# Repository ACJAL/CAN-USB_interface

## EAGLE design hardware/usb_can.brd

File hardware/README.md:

# Hardware
---

Fichiers de conception de la carte éléctronique. Le PCB a été réalisé avec le logiciel *eagle* de *CADsoft*.

+ [Schéma *fichier eagle SCH*](usb_can.sch)
+ [Schéma *fichier PDF*](usb_can_sch.pdf)
+ [Routage *fichier eagle BRD*](usb_can.brd)
+ [DOC](usb_can_doc_hard.pdf) (La documention de la carte a été réalisée avec *LaTeX*)

## Synoptique de la carte

Le coeur de l'interface est un PIC18F2580. Microcontroleur 8 bits, possédant un module bus CAN intégré.

La partie communication USB est réalisé par un MCP2210. Ce composant est une interface USB vers SPI qui nécessite très peu de composants pour être mis en oeuvre.

L'interface bus CAN (liaison matérielle) est réalisée par un MCP2561.

Enfin, un interrupteur sur la carte éléctronique permet de *terminer* ou non le bus avec une résistance de 120 Ohms.

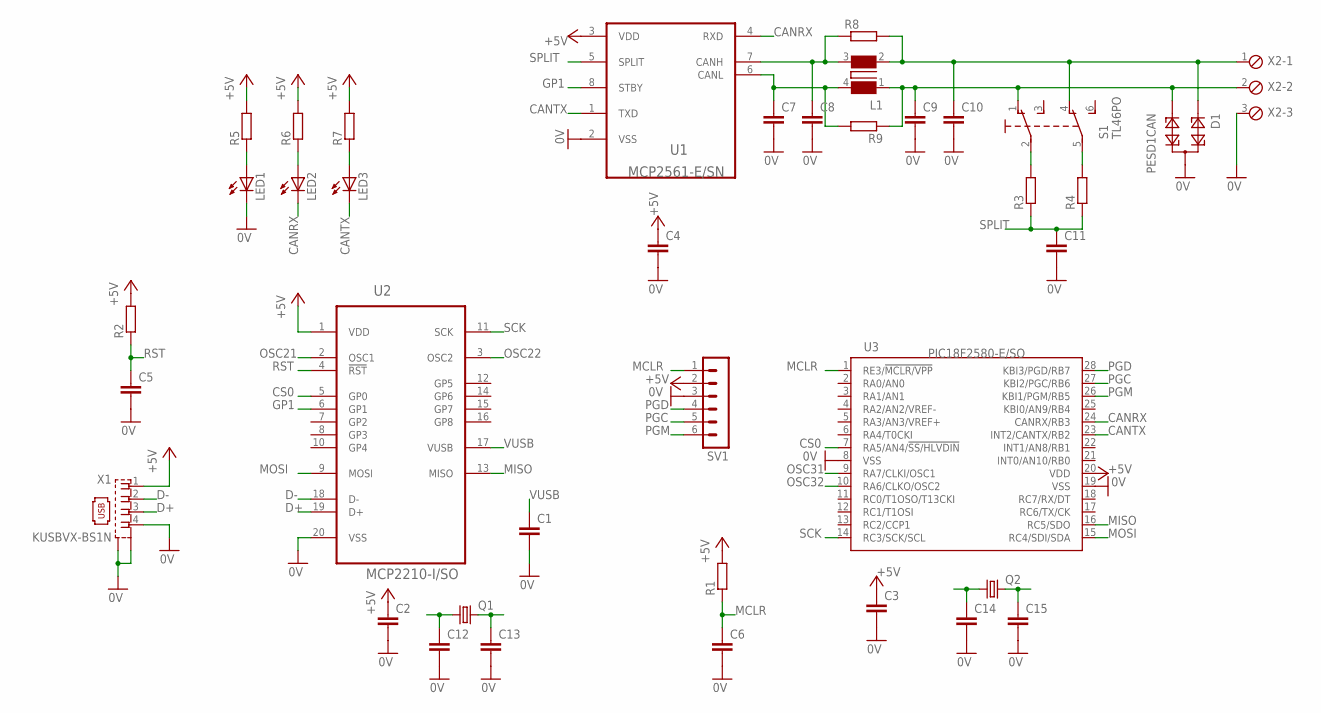
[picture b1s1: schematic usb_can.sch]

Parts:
C1: C-EUC1210; C1210
C2, C3, C4, C5, C6, C7, C8, C9, C10, C11, C12, C13, C14, C15: C-EUC0805; C0805
D1: PESD1CAN; SOT23
L1: WE-SLM-744242510; WE-SLM
LED1, LED2, LED3: LED3MM
Q1, Q2: CRYSTALHC49UP; HC49UP
R1, R2, R5, R6, R7: R-EU_R0805; R0805
R3, R4, R8, R9: R-EU_MELF0204W; MINI_MELF-0204W
S1: TL46PO; TL4XPO
SV1: MA06-1
U1: MCP2561-E/SN; SOIC127P600X175-8N
U2: MCP2210-I/SO; SOIC127P1030X265-20N
U3: PIC18F2580-E/SO; SO28W
X1: KUSBVX-BS1N
X2: MPT3; 3POL254

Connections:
0V: C1.2, C2.2, C3.2, C4.2, C5.2, C6.2, C7.2, C8.2, C9.2, C10.2, C11.2, C12.2, C13.2, C14.2, C15.2, D1.3, LED1.K (C), SV1.3, U1.2 (VSS), U2.20 (VSS), U3.8 (VSS), U3.19 (VSS), X1.4, X1.M1 (S1), X1.M2 (S2), X2.3
+5V: C2.1, C3.1, C4.1, R1.2, R2.2, R5.2, R6.2, R7.2, SV1.2, U1.3 (VDD), U2.1 (VDD), U3.20 (VDD), X1.1
CANRX: LED2.K (C), U1.4 (RXD), U3.24 (CANRX/RB3)
CANTX: LED3.K (C), U1.1 (TXD), U3.23 (INT2/CANTX/RB2)
CS0: U2.5 (GP0), U3.7 (RA5/AN4/!SS/HLVDIN)
D+: U2.19 (D+), X1.3
D-: U2.18 (D-), X1.2
GP1: U1.8 (STBY), U2.6 (GP1)
MCLR: C6.1, R1.1, SV1.1, U3.1 (RE3/!MCLR/VPP)
MISO: U2.13 (MISO), U3.16 (RC5/SDO)
MOSI: U2.9 (MOSI), U3.15 (RC4/SDI/SDA)
unnamed: R3.2, S1.2
unnamed: LED3.A, R7.1
unnamed: R4.2, S1.5 (P1)
unnamed: C8.1, L1.3 (2), R8.1, U1.7 (CANH)
unnamed: C7.1, L1.4, R9.2, U1.6 (CANL)
unnamed: C9.1, D1.2, L1.1 (3), R9.1, S1.1 (O), X2.2
unnamed: C10.1, D1.1, L1.2 (1), R8.2, S1.4 (O1), X2.1
unnamed: LED2.A, R6.1
unnamed: LED1.A, R5.1
OSC21: C12.1, Q1.1, U2.2 (OSC1)
OSC22: C13.1, Q1.2, U2.3 (OSC2)
OSC31: C14.1, Q2.1, U3.9 (RA7/CLKI/OSC1)
OSC32: C15.1, Q2.2, U3.10 (RA6/CLKO/OSC2)
PGC: SV1.5, U3.27 (KBI2/PGC/RB6)
PGD: SV1.4, U3.28 (KBI3/PGD/RB7)
PGM: SV1.6, U3.26 (KBI1/PGM/RB5)
RST: C5.1, R2.1, U2.4 (!RST)
SCK: U2.11 (SCK), U3.14 (RC3/SCK/SCL)
SPLIT: C11.1, R3.1, R4.1, U1.5 (SPLIT)
VUSB: C1.1, U2.17 (VUSB)

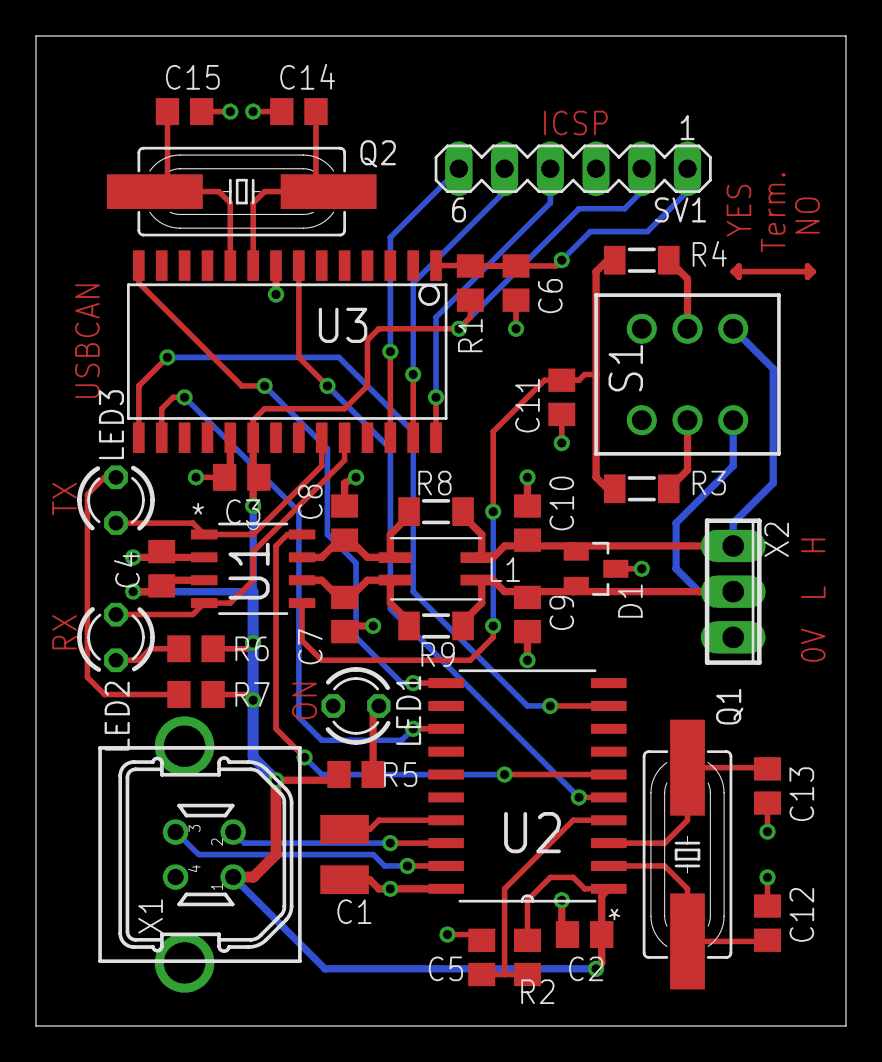
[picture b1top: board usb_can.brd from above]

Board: 2 copper layers, 45.0 x 55.0 mm, 38 parts (0 on the bottom side), 31 nets.

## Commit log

2018-07-25 SCH and BRD board addition
2018-07-26 DOC addition
